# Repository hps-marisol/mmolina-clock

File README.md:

# mmolina-clock
 my first clock

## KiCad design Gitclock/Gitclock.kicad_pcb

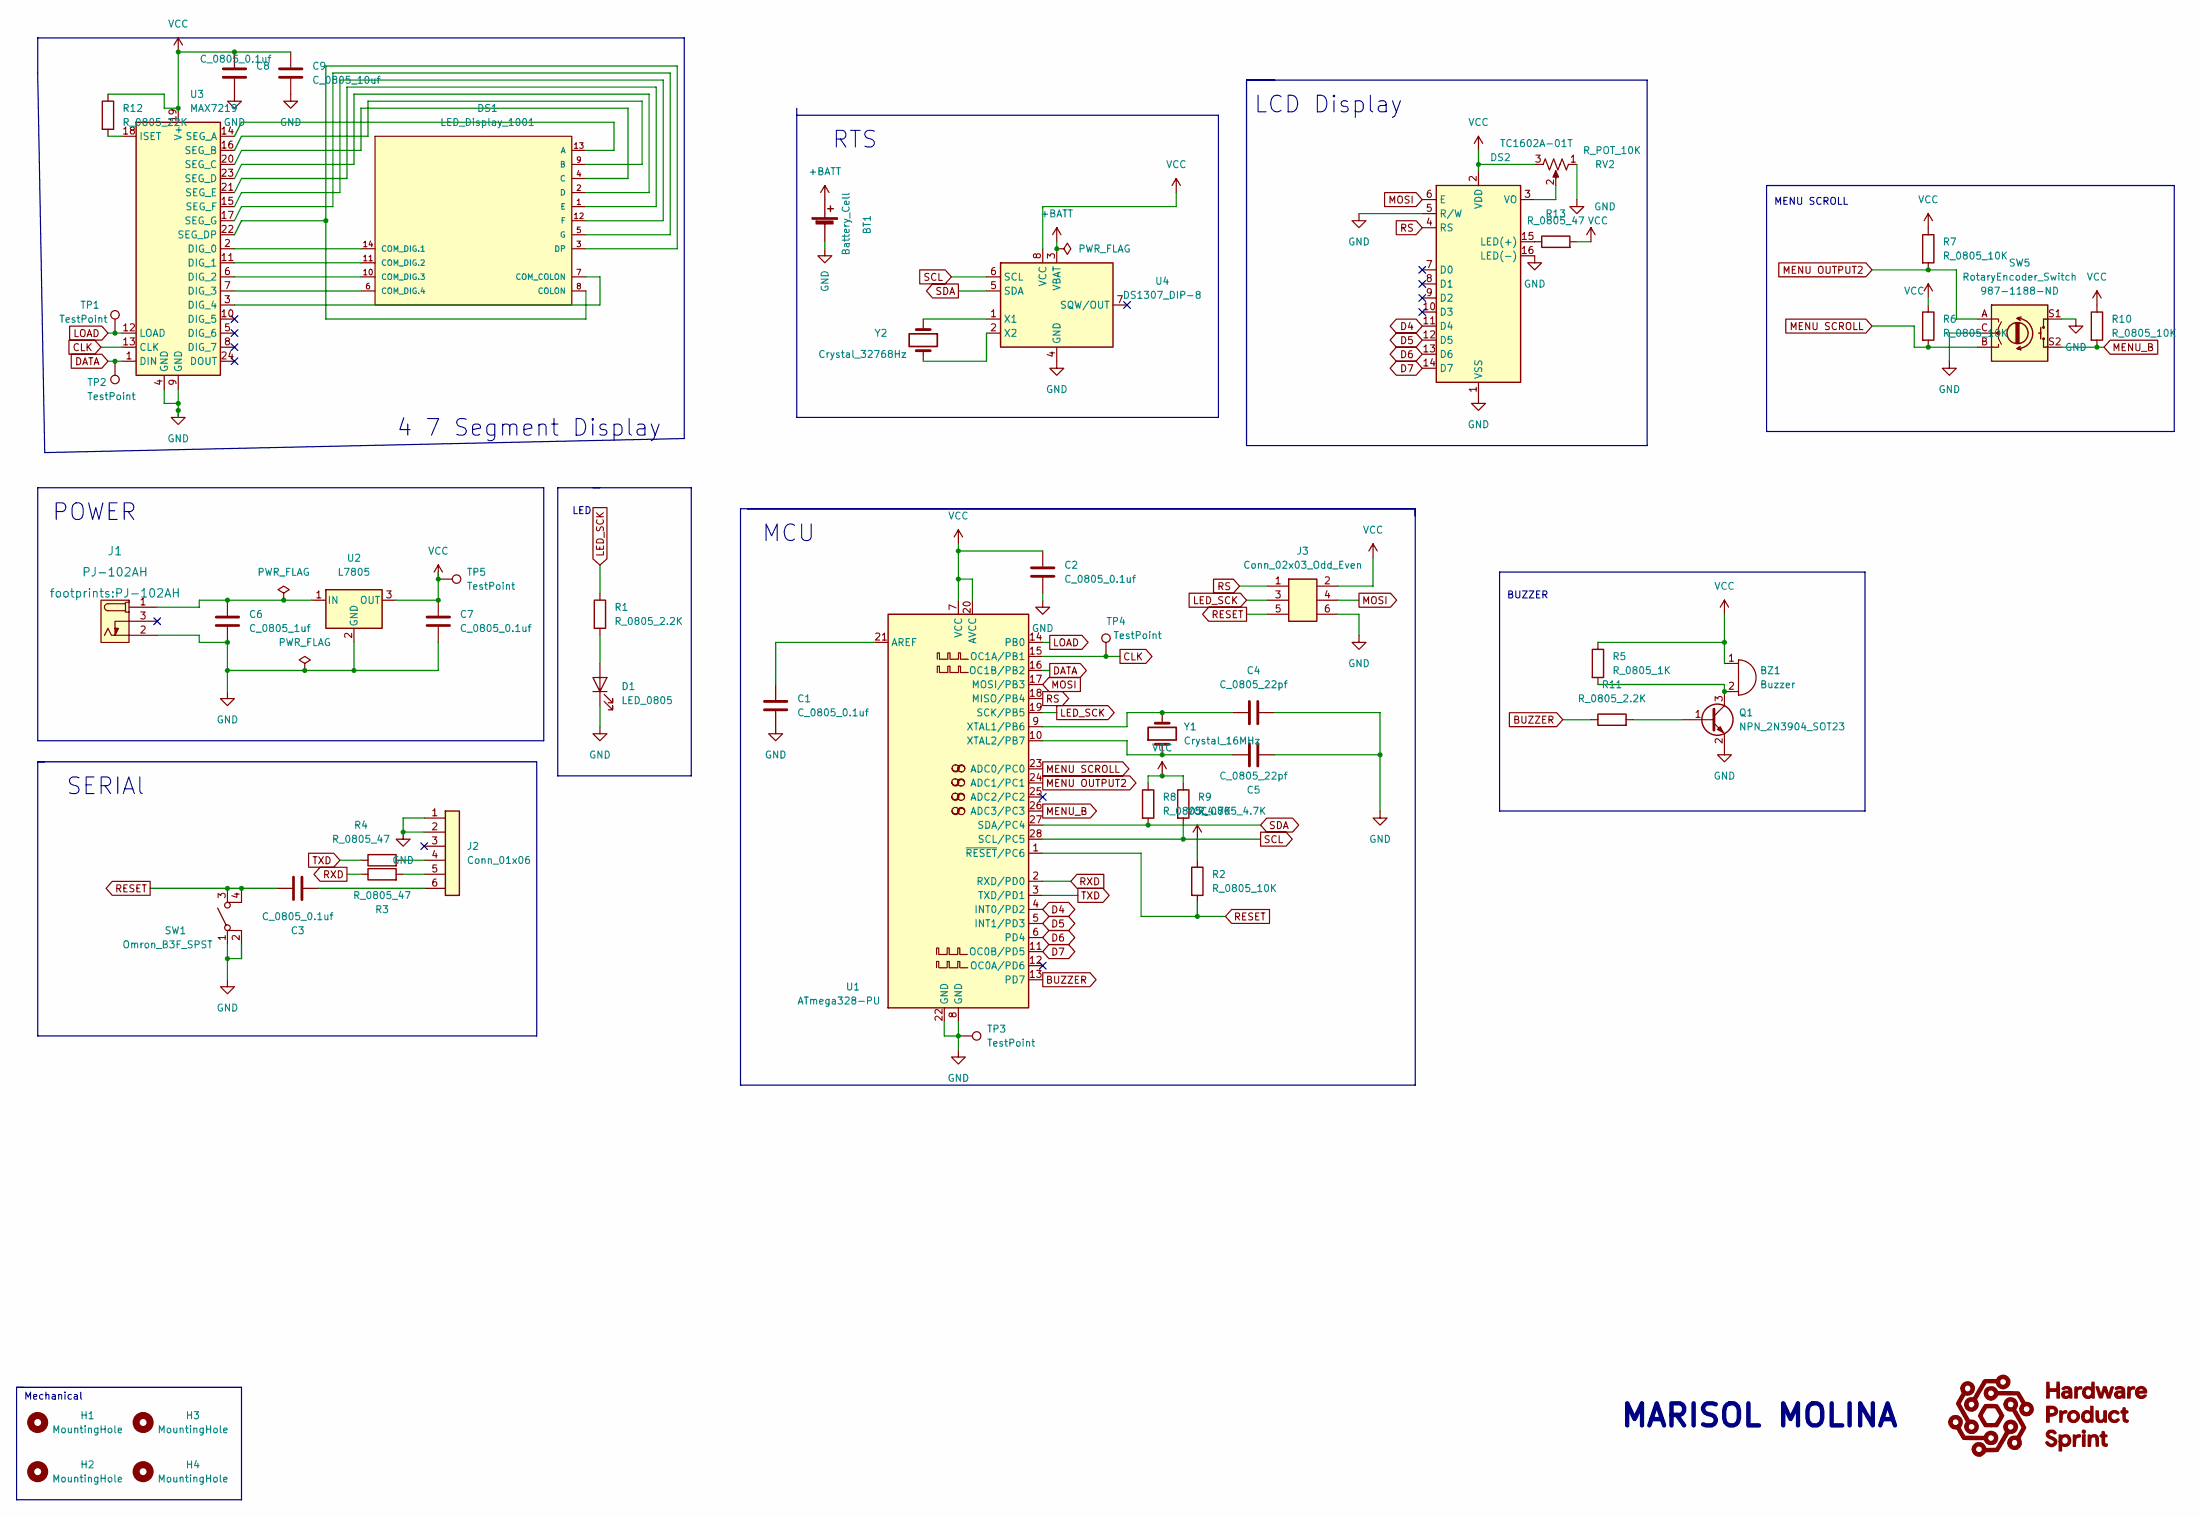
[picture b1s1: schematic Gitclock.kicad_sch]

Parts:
BT1: Battery_Cell; BatteryHolder_Keystone_106_1x20mm; MPN BS-7; Digikey PN BS-7-ND
BZ1: Buzzer; Buzzer_TDK_PS1240P02BT_D12.2mm_H6.5mm; MPN PS1420P02CT; Digikey PN 445-2526-1-ND
C1, C2, C3, C7, C8: C_0805_0.1uf; C_0805_2012Metric; Voltage N/A; Tolerance N/A; MPN 08055C104KAT2A; Digikey PN 478-1395-1-ND
C4, C5: C_0805_22pf; C_0805_2012Metric; Voltage N/A; Tolerance N/A; MPN CC0805JRNPO9BN220; Digikey PN 311-1103-1-ND
C6: C_0805_1uf; C_0805_2012Metric; Voltage N/A; Tolerance N/A; MPN CC0805KKX7R8BB105; Digikey PN 311-1456-1-ND
C9: C_0805_10uf; C_0805_2012Metric; Voltage N/A; Tolerance N/A; MPN GRM21BR61E106KA73L; Digikey PN 490-5523-1-ND
D1: LED_0805; LED_0805_2012Metric; MPN 150080RS75000; Digikey PN 732-4984-1-ND
DS1: LED_Display_1001; Adafruit-1001-0-0-MFG; forward voltage 3.2V; reverse voltage 5V; mouser part number 485-1001; digikey description WHITE 7-SEGMENT CLOCK DISPLAY
DS2: TC1602A-01T; MPN 1447; Digikey PN 1528-2212-ND
H1, H2, H3, H4: MountingHole; MountingHole_3.2mm_M3
J1: PJ-102AH; MPN PJ-102AH; Digikey PN CP-102AH-ND
J2: Conn_01x06; PinHeader_1x06_P2.54mm_Vertical; MPN 61300611121; Digikey PN 732-5319-ND
J3: Conn_02x03_Odd_Even; PinHeader_2x03_P2.54mm_Vertical; MPN PRPC003DAAN-RC; Digikey PN S2011EC-03-ND
Q1: NPN_2N3904_SOT23; SOT-23; MPN CMPT3904E TR PBFREE; Digikey PN 1514-CMPT3904ETRPBFREECT-ND
R1, R11: R_0805_2.2K; R_0805_2012Metric; Tolerance N/A; MPN N/A; Digikey PN 311-2.20KCRCT-ND
R2, R6, R7, R10: R_0805_10K; R_0805_2012Metric; Tolerance N/A; MPN RC0805FR-0710KL; Digikey PN 311-10.0KCRCT-ND
R3, R4, R13: R_0805_47; R_0805_2012Metric; Tolerance N/A; Mouser PN N/A; Digikey PN RC0805FR-0747RL
R5: R_0805_1K; R_0805_2012Metric; Tolerance N/A; Mouser PN N/A; Digikey PN RC0805FR-0710KL
R8, R9: R_0805_4.7K; R_0805_2012Metric; Tolerance N/A; MPN RC0805FR-074K7L; Digikey PN 311-4.70KCRCT-ND
R12: R_0805_22K; R_0805_2012Metric; Tolerance N/A; MPN RC0805FR-0722KL; Digikey PN 311-22.0KCRCT-ND
RV2: R_POT_10K; Potentiometer_Bourns_3386P_Vertical; MPN 3386P-1-103TLF; Digikey PN 3386P-103TLF-ND
SW1: Omron_B3F_SPST; SW_SPST_Omron_B3FS-100xP; MPN B3FS-1000P; Digikey PN SW423CT-ND
SW5: RotaryEncoder_Switch; RotaryEncoder_TT_EN11-Switch_Vertical_H20mm_CircularMountin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; Digikey PN 987-1188-ND
TP1, TP2, TP3, TP4, TP5: TestPoint; TestPoint_THTPad_D2.0mm_Drill1.0mm
U1: ATmega328-PU; DIP-28_W7.62mm; MPN ED281DT; Digikey PN ED3050-5-ND
U2: L7805; TO-252-2; MPN L7805CDT-TR; Digikey PN 497-7255-1-ND
U3: MAX7219; DIP-24_W7.62mm; MPN ED241DT; Digikey PN ED3049-5-ND
U4: DS1307_DIP-8; DIP-8_W7.62mm; MPN A 08-LC-TT; Digikey PN AE9986-ND
Y1: Crystal_16MHz; Crystal_SMD_HC49-SD; MPN ECS-160-20-5PXDN-TR; Digikey PN XC1299CT-ND
Y2: Crystal_32768Hz; Crystal_SMD_2Pin_3.2x1.5mm; MPN Q 0,032768-JTX310-12,5-20-T1-HMR-50K-LF; Digikey PN 1908-1314-1-ND

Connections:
+BATT: BT1.1 (+), U4.3 (VBAT)
BUZZER: R11.1, U1.13 (PD7)
CLK: TP4.1, U1.15 (OC1A/PB1), U3.13 (CLK)
D4: DS2.11 (D4), U1.4 (INT0/PD2)
D5: DS2.12 (D5), U1.5 (INT1/PD3)
D6: DS2.13 (D6), U1.6 (PD4)
D7: DS2.14 (D7), U1.11 (OC0B/PD5)
DATA: TP2.1, U1.16 (OC1B/PB2), U3.1 (DIN)
GND: BT1.2 (-), C1.2, C2.2, C4.2, C5.2, C6.2, C7.2, C8.2, C9.2, D1.1 (K), DS2.1 (VSS), DS2.5 (R/W), DS2.16 (LED(-)), J1.2 (OUT), J2.1, J2.2, J3.6, Q1.2 (E), RV2.1, SW1.1 (A), SW1.2 (A), SW5.C, SW5.S1, TP3.1, U1.8 (GND), U1.22 (GND), U2.2 (GND), U3.4 (GND), U3.9 (GND), U4.4 (GND)
LED_SCK: J3.3, R1.1, U1.19 (SCK/PB5)
LOAD: TP1.1, U1.14 (PB0), U3.12 (LOAD)
MENU OUTPUT2: R7.2, SW5.A, U1.24 (ADC1/PC1)
MENU SCROLL: R6.2, SW5.B, U1.23 (ADC0/PC0)
MENU_B: R10.2, SW5.S2, U1.26 (ADC3/PC3)
MOSI: DS2.6 (E), J3.4, U1.17 (MOSI/PB3)
unnamed: BZ1.2 (+), Q1.3 (C), R5.2
unnamed: C1.1, U1.21 (AREF)
unnamed: C3.2, J2.6
unnamed: C4.1, U1.9 (XTAL1/PB6), Y1.2
unnamed: C5.1, U1.10 (XTAL2/PB7), Y1.1
unnamed: C6.1, J1.1 (POLE), U2.1 (IN)
unnamed: D1.2 (A), R1.2
unnamed: DS1.1 (E), U3.21 (SEG_E)
unnamed: DS1.2 (D), U3.23 (SEG_D)
unnamed: DS1.3 (DP), DS1.8 (COLON), U3.22 (SEG_DP)
unnamed: DS1.4 (C), U3.20 (SEG_C)
unnamed: DS1.5 (G), U3.17 (SEG_G)
unnamed: DS1.6 (COM_DIG.4), U3.7 (DIG_3)
unnamed: DS1.7 (COM_COLON), U3.3 (DIG_4)
unnamed: DS1.9 (B), U3.16 (SEG_B)
unnamed: DS1.10 (COM_DIG.3), U3.6 (DIG_2)
unnamed: DS1.11 (COM_DIG.2), U3.11 (DIG_1)
unnamed: DS1.12 (F), U3.15 (SEG_F)
unnamed: DS1.13 (A), U3.14 (SEG_A)
unnamed: DS1.14 (COM_DIG.1), U3.2 (DIG_0)
unnamed: DS2.3 (VO), RV2.2
unnamed: DS2.15 (LED(+)), R13.1
unnamed: J2.4, R4.2
unnamed: J2.5, R3.2
unnamed: Q1.1 (B), R11.2
unnamed: R12.2, U3.18 (ISET)
unnamed: U4.1 (X1), Y2.1
unnamed: U4.2 (X2), Y2.2
RESET: C3.1, J3.5, R2.2, SW1.3 (B), SW1.4 (B), U1.1 (~RESET/PC6)
RS: DS2.4 (RS), J3.1, U1.18 (MISO/PB4)
RXD: R3.1, U1.2 (RXD/PD0)
SDA: R8.2, U1.27 (SDA/PC4), U4.5 (SDA)
TXD: R4.1, U1.3 (TXD/PD1)

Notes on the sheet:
SERIAl
4 7 Segment Display
LED
BUZZER
LCD Display
MENU SCROLL
Mechanical
MARISOL MOLINA
MCU
RTS
POWER

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
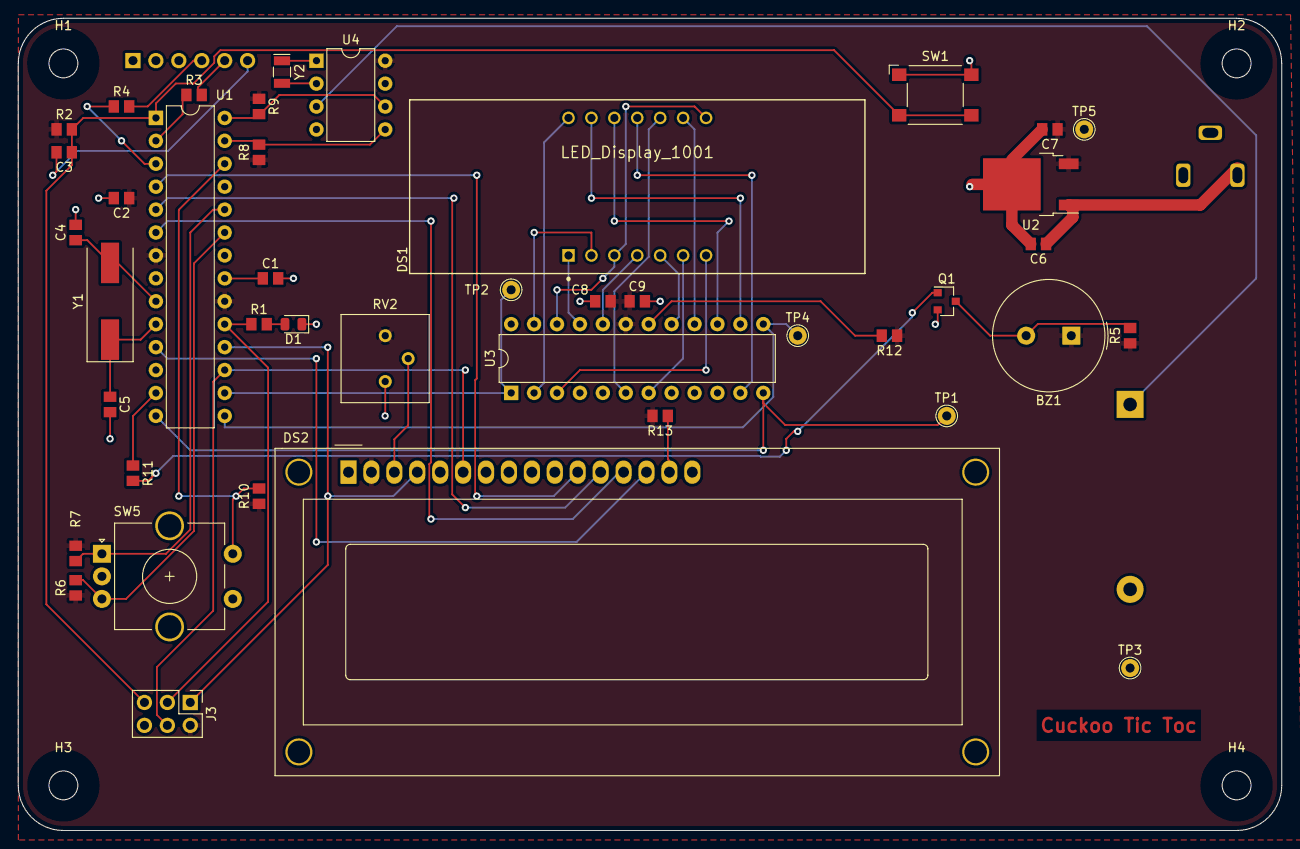
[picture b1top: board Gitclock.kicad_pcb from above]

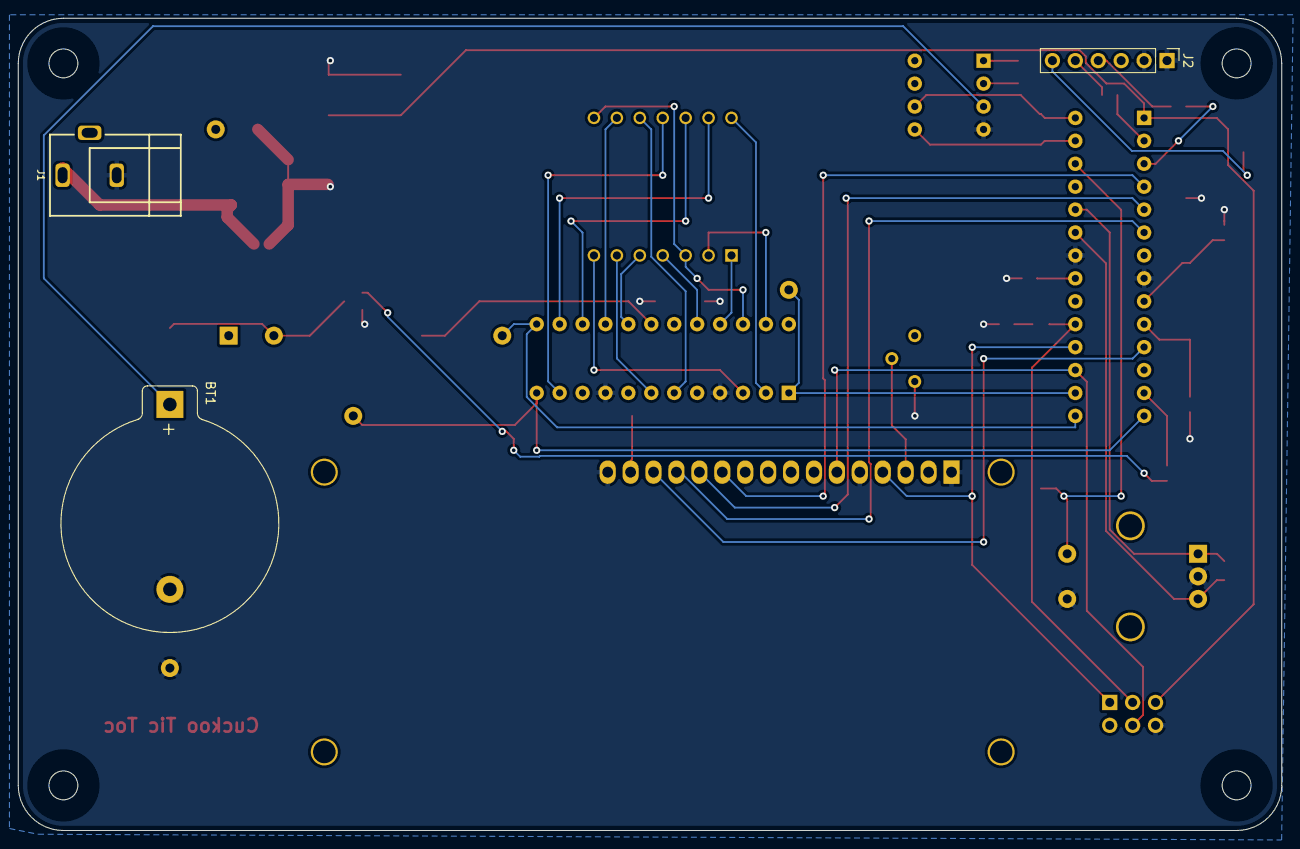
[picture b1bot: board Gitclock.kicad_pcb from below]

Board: 2 copper layers, 140.0 x 90.0 mm, 49 parts (3 on the bottom side), 50 nets.

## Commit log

2022-06-05 My First HPS Design
2022-06-08 practiceupload
2022-06-13 Blinking Lights Firmware
2022-06-13 Gitclock
2022-06-20 Week 2: Clock Schematic
2022-06-20 Switchcode
    Button changes serial output from stating button is being pressed and not pressed
2022-06-29 Update Gitclock
2022-06-29 Updatedclock
2022-06-30 gitclock6302022
2022-07-04 Clock20220704
    11:06 AM
2022-07-06 Updatedclock
    20220705
    6:27PM
2022-07-07 Gitclock
    20220707
    9:46AM
2022-07-07 20220707Clock
    12:22PM
2022-07-07 Latest: 20220707
    12:32PM Gitclock Update
2022-07-07 Gitclock
    20220707
    1:15PM
2022-07-07 Gitclock
    20220707
    3:55PM
2022-07-14 20220713
    5:40 PM clock
2022-07-20 0719clock
2022-07-20 clock0719
2022-07-20 Routing display
2022-07-20 Final Routing Pass
2022-07-20 Final Routing Design
    Still need to finish last two routes
2022-07-20 Finished Routing each individual connections
    Waiting for approval
2022-07-20 Test Points Added to Clock
2022-07-21 clock_complete
2022-07-22 CuckcooTicTocFINALCLOCK
    Last Upload onto Github
2022-07-22 changed pull down to pull up and swapped RX and TX connection
2022-07-23 Changed Encoder connection on SW from VCC to GND
2022-07-23 Finalcuckcootictoc clock
    Made edits according to final checklist
